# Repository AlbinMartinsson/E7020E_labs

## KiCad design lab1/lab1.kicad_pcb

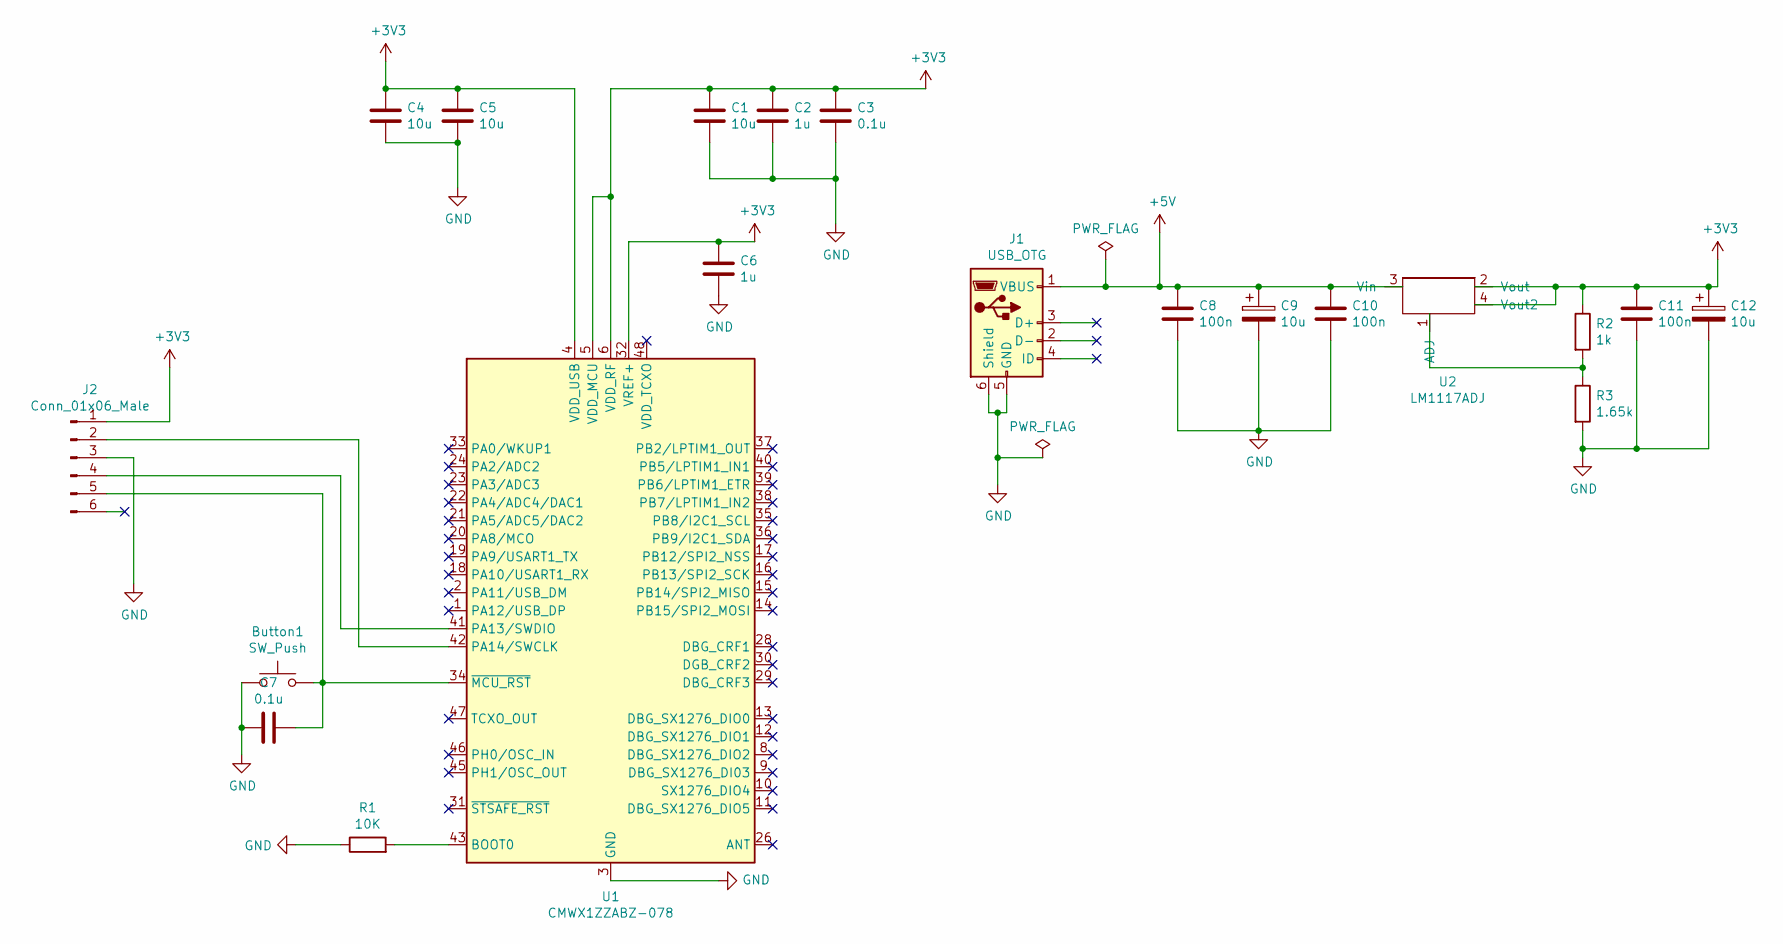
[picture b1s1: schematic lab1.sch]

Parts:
Button1: SW_Push; SW_Push_1P1T_NO_6x6mm_H9.5mm
C1, C4, C5: 10u; C_0805_2012Metric_Pad1.15x1.40mm_HandSolder
C2, C6: 1u; C_0805_2012Metric_Pad1.15x1.40mm_HandSolder
C3, C7: 0.1u; C_0805_2012Metric_Pad1.15x1.40mm_HandSolder
C8, C10, C11: 100n; C_0805_2012Metric_Pad1.15x1.40mm_HandSolder
C9, C12: 10u; CP_Elec_5x4.5
J1: USB_OTG; USB_Micro-B_Wuerth_629105150521
J2: Conn_01x06_Male; PinHeader_1x06_P2.54mm_Vertical
R1: 10K; R_0805_2012Metric_Pad1.15x1.40mm_HandSolder
R2: 1k; R_0805_2012Metric_Pad1.15x1.40mm_HandSolder
R3: 1.65k; R_0805_2012Metric_Pad1.15x1.40mm_HandSolder
U1: CMWX1ZZABZ-078; CMWX1ZZABZ
U2: LM1117ADJ; SOT-223

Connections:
+3V3: C1.1, C2.1, C3.1, C4.1, C5.1, C6.1, C11.1, C12.1, J2.1, R2.1, U1.4 (VDD_USB), U1.5 (VDD_MCU), U1.6 (VDD_RF), U1.32 (VREF+), U2.2 (Vout), U2.4 (Vout2)
+5V: C8.1, C9.1, C10.1, J1.1 (VBUS), U2.3 (Vin)
GND: Button1.1, C1.2, C2.2, C3.2, C4.2, C5.2, C6.2, C7.1, C8.2, C9.2, C10.2, C11.2, C12.2, J1.5 (GND), J1.6 (Shield), J2.3, R1.1, R3.2, U1.3 (GND), U1.7 (GND), U1.25 (GND), U1.27 (GND), U1.44 (GND), U1.49 (GND), U1.50 (GND), U1.51 (GND), U1.52 (GND), U1.53 (GND), U1.54 (GND), U1.55 (GND), U1.56 (GND), U1.57 (GND)
unnamed: Button1.2, C7.2, J2.5, U1.34 (~MCU_RST)
unnamed: J2.2, U1.42 (PA14/SWCLK)
unnamed: J2.4, U1.41 (PA13/SWDIO)
unnamed: R1.2, U1.43 (BOOT0)
unnamed: R2.2, R3.1, U2.1 (ADJ)

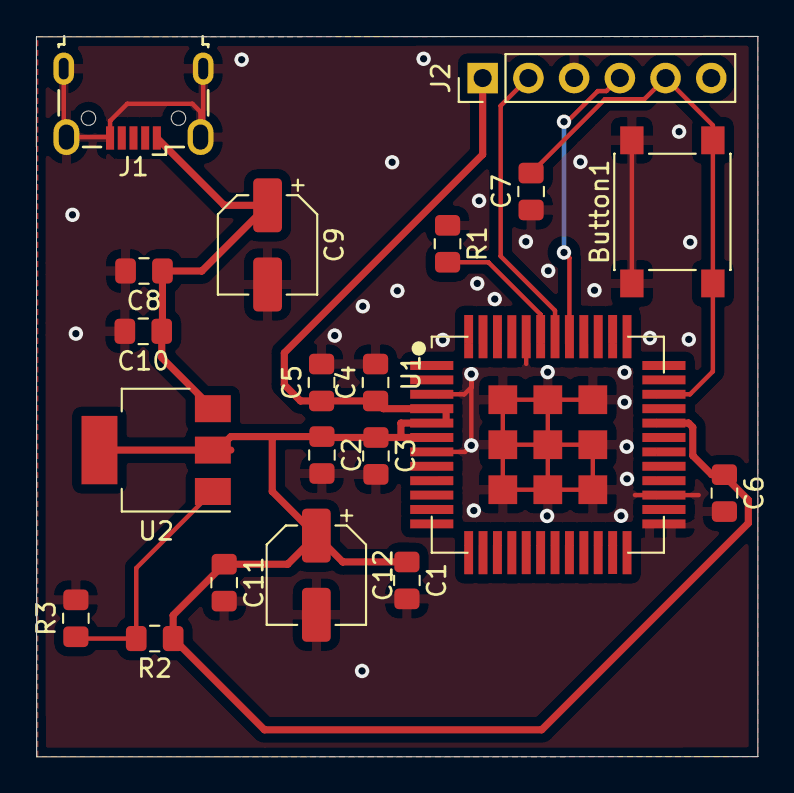
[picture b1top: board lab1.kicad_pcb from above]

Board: 2 copper layers, 40.1 x 40.0 mm, 20 parts (0 on the bottom side), 8 nets.

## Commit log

2020-04-10 fixed repo porblems
2020-04-15 Fixed config
2020-04-15 Added to -gitignore
2020-04-15 bare1_1
2020-04-15 bare1_2
2020-04-16 bare1_3
2020-04-16 Bare1_4
2020-04-16 Bare1_4, real commit
2020-04-16 bare2_1
2020-04-16 bare3_1
2020-04-16 bare3_2
2020-04-20 bare3_3
2020-04-20 bare3_4
2020-04-20 bare3_5
2020-04-20 bare4_1
2020-04-20 bare4_2
2020-04-20 bare4_3
2020-04-21 bare5_1
2020-04-21 bare5_2
